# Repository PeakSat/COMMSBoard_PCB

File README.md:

# SatNOGS COMMS hardware

A CubeSat format ([LibreCube Board](https://wiki.librecube.org/index.php?title=LibreCube_Board_Specification)) COMMS board.
It supports UHF and S-Band concurrent half duplex (in each band) communication.
More details could be found [here](https://gitlab.com/librespacefoundation/satnogs-comms/satnogs-comms-design-doc).

Stable versions are tagging with TBD.

## Contribute
This is a KiCAD project thus merging can be tricky.
Coordinate with project engineers before starting any changes and take look at issues.

## EDA
KiCAD 6

Requires [lsf-kicad-lib](https://gitlab.com/librespacefoundation/lsf-kicad-lib) to be installed.
Set path LSF_KICAD_LIB to point to lsf-kicad-lib folder for 3D models to appear correctly

#### Schematic
Changes in manufacturer part numbers field, footprints and designators can be merged most of the times.
Any part change, change in placement, wire placement etc cannot be merged at this point.

One exception is Hierarchical sheets provided that:

* A single person is working on a Hierarchical sheet
* Annotation is using sheet number
* Global nets are respected
* Changes in Hierarchical labels are coordinated

#### PCB
At this point any merging on PCB files must be avoided.
Also for the PCB (*.kicad_pcb) is used [LFS](https://docs.gitlab.com/ee/topics/git/lfs/) to prevent
a large size repository and to use the feature of LFS lock. The LFS lock protects the developers
to have conflicts in PCB that aren't merged. For that reason use:

```
git lfs clone
```

to clone the repository.

## Simulation
[Qucs 0.0.20](https://github.com/Qucs/qucs).

## License
Licensed under the [CERN OHLv1.2](LICENSE)

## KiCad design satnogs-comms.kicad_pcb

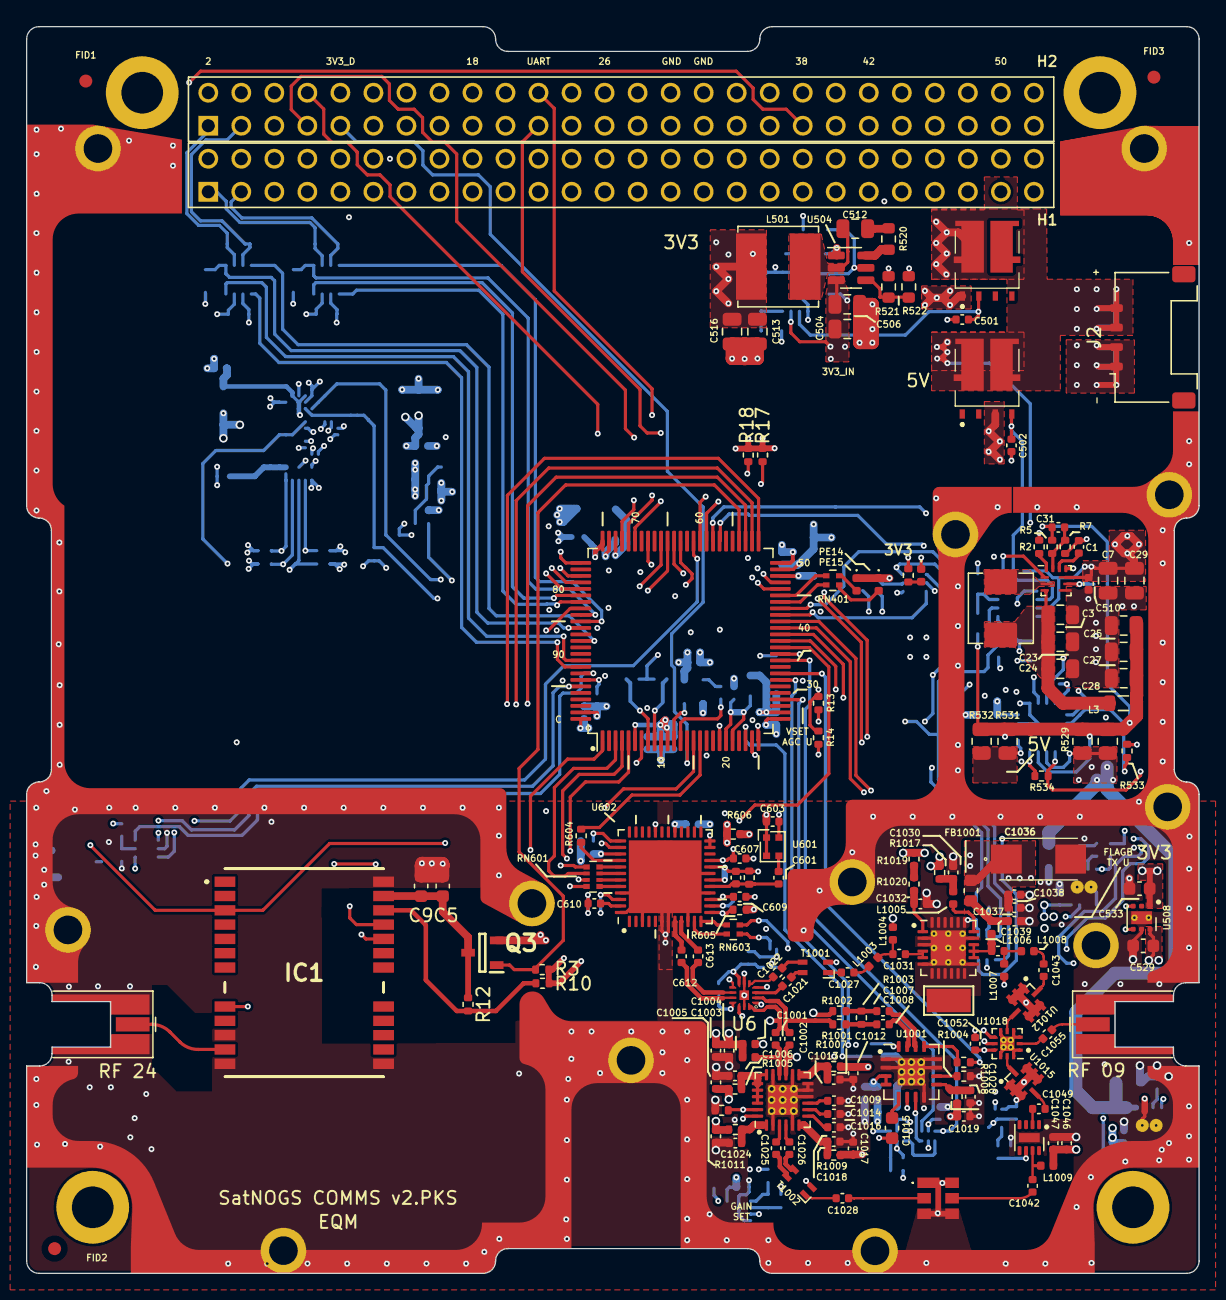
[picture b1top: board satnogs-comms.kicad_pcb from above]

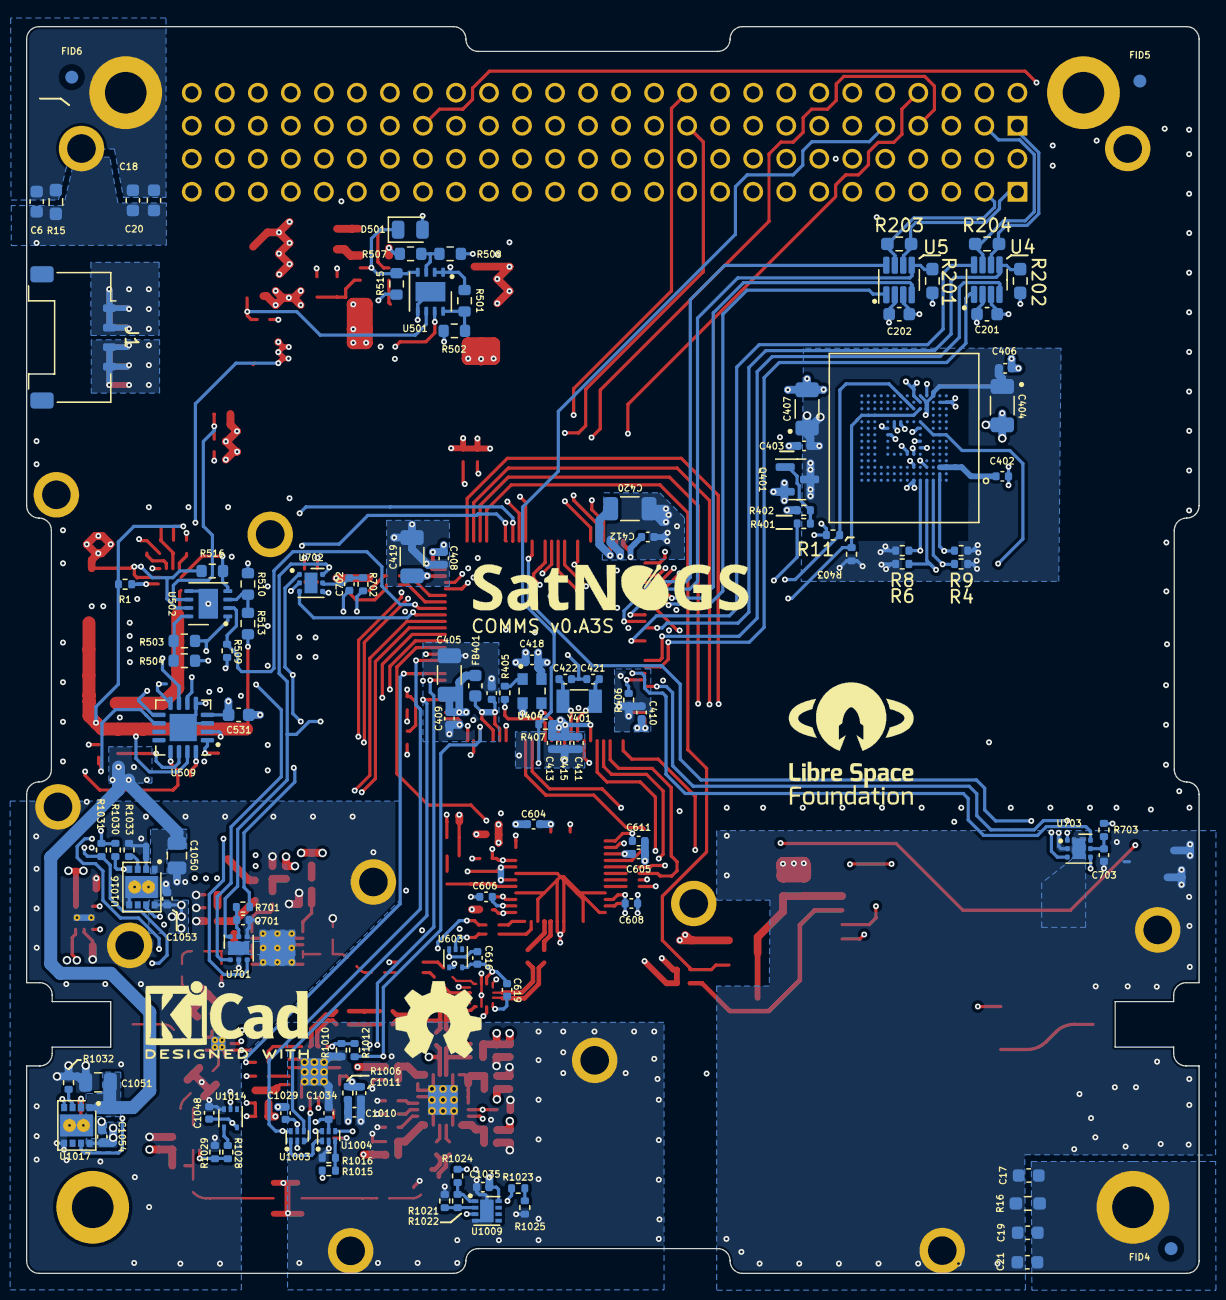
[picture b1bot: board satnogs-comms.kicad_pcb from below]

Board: 6 copper layers, 90.2 x 95.9 mm, 288 parts (124 on the bottom side), 202 nets.

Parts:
ANT-S901: RF 24; MMCX_Molex_73415-0961_Horizontal_1.6mm-PCB
ANT-U1001: RF 09; MMCX_Molex_73415-0961_Horizontal_1.6mm-PCB
C1: 470n; C_0402_1005Metric
C2, C31, C402, C403, C406, C408, C409, C410, C411, C412, C413, C415, C418, C501, C502, C603, C604, C605, C607, C608, C609, C701, C702, C703, C1003, C1005, C1010, C1012, C1017, C1019, C1023, C1030, C1048, C1053, C1054: 100n; C_0402_1005Metric
C3, C23, C24, C25, C27, C28: 22uF; C_0805_2012Metric
C5: 10u; C_0603_1608Metric
C6, C17, C18, C19, C20, C21: 1n; C_0603_1608Metric
C7, C29: 6.8u; C_0805_2012Metric
C9, C201, C202, C531: 100n; C_0603_1608Metric
C404, C405, C407: 4.7u; C_1206_3216Metric
C419, C420: 2.2u; C_1206_3216Metric
C421, C422: 12p; C_0402_1005Metric
C504, C1050, C1051: 10u; C_0805_2012Metric
C506, C512: 100n; C_0805_2012Metric
C510: 2.2n; C_0402_1005Metric
C513, C516: 22u; C_0805_2012Metric
C529, C533: 1u; C_0603_1608Metric
C601, C1007, C1008, C1009, C1014, C1016, C1037: 1n; C_0402_1005Metric
C602: 10p; C_0402_1005Metric
C606, C610, C611, C1046: 1u; C_0402_1005Metric
C612, C613, C616, C619, C1001, C1002, C1004, C1006, C1011, C1013, C1018, C1020, C1021, C1022, C1024, C1025, C1026, C1028, C1032, C1038, C1039, C1042, C1047, C1049, C1052, C1055: 100p; C_0402_1005Metric
C1015: 220pF; C_0603_1608Metric
C1027: 2p; C_0402_1005Metric
C1029, C1034, C1035: 10n; C_0402_1005Metric
C1031: 62p; C_0402_1005Metric
C1036: 10u; T495C
C1040: 24p; C_0402_1005Metric
C1043: 3.3p; C_0402_1005Metric
D401: PE14; LED_0402_1005Metric
D402: PE15; LED_0402_1005Metric
D501: 3.6V; D_0805_2012Metric
D502: 3V3; LED_0402_1005Metric
FB401, FB1001: Ferrite_Bead; L_0603_1608Metric
FID1, FID2, FID3, FID4, FID5, FID6: Fiducial; Fiducial_1mm_Mask2mm
FL2: SF2446E
H111, H112, H113, H114: MountingHole_Pad; MountingHole_3.2mm_M3_DIN965_Pad
IC1: B1601
J1, J2: Conn_01x04; Molex_Pico-Lock_504050-0491_1x04-1MP_P1.50mm_Horizontal
J102: Η1; ESQ-126-39-x-D
J103: Η2; ESQ-126-39-x-D
J104: RFShield_OnePiece; emi-shield-original
L2: 2.2u; L_Abracon_ASPI-0530HI
L3: 0u; L_0805_2012Metric
L501: 4.7u; L_Bourns_SRN6045TA
L1001, L1002: 120n; L_0402_1005Metric
L1003, L1005, L1009: 68n; L_0402_1005Metric
L1004: 3.2n; L_0402_1005Metric
L1006: 18n; L_0402_1005Metric
L1007: 8.2n; L_0402_1005Metric
L1008: 47n; L_0402_1005Metric
NT1, NT601, NT1001, NT1002: Net-Tie_2; NetTie-2_SMD_Pad0.5mm
Q1, Q2: SQJB90EP-T1_GE3; SQJ910AEPT1_GE3
Q3: PMV28XPEAR; SOT95P230X110-3N
Q401: FDN308P; SOT-23
R1, R402, R605, R1030, R1031: 100k; R_0402_1005Metric
R2: 18.2k; R_0402_1005Metric
R3, R4, R6, R8, R9, R11, R406, R509, R533, R534, R603, R1010, R1011, R1029: 10k; R_0402_1005Metric
R5: 25.5k; R_0402_1005Metric
R7: 4.87k; R_0402_1005Metric
R10, R405, R606, R1004, R1005, R1006, R1007, R1008, R1009, R1012, R1014, R1020, R1021, R1022, R1024: 0; R_0402_1005Metric
R12, R407: DNP; R_0402_1005Metric
R13, R14, R17, R18: 5k; R_0402_1005Metric
R15, R16: 100k; R_0603_1608Metric_Pad0.98x0.95mm_HandSolder
R201, R202: 10k; R_0603_1608Metric_Pad0.98x0.95mm_HandSolder
R203, R204: 120; R_0603_1608Metric_Pad0.98x0.95mm_HandSolder
R401, R1013, R1015, R1023: 1k; R_0402_1005Metric
R403: 4.7k; R_0402_1005Metric
R501: 200k; R_0603_1608Metric
R502, R504, R507: 100k; R_0603_1608Metric
R503: 345k; R_0603_1608Metric
R508: 620k; R_0603_1608Metric
R510: 73.2k; R_0603_1608Metric
R513: 706k; R_0603_1608Metric
R515, R516: 2.2k; R_0603_1608Metric
R520: 30; R_0603_1608Metric
R521: 30.9k; R_0603_1608Metric
R522: 10k; R_0603_1608Metric
R529, R530, R531, R532: 0.02; R_0805_2012Metric
R537: 330; R_0402_1005Metric
R604: 470; R_0402_1005Metric
R701, R702, R703: 500; R_0402_1005Metric
R1001, R1002: 82; R_0402_1005Metric
R1003: 52.3; R_0402_1005Metric
R1016: 412; R_0402_1005Metric
R1017: 240; R_0402_1005Metric
R1019: 280; R_0402_1005Metric
R1025: 2.2k; R_0402_1005Metric
R1028: 33k; R_0402_1005Metric
R1032: 374k; R_0402_1005Metric
R1033: 110k; R_0402_1005Metric
RN401: 330; R_Array_Convex_2x0402
RN601: 470; R_Array_Convex_4x0402
RN603: R_Pack02; R_Array_Convex_2x0402
T1001, T1002: Transformer_1P_1S; ATB2012
TP1011: TestPoint; TestPoint_Keystone_5015_Micro-Minature
U1: STM32H743VITx; LQFP-100_14x14mm_P0.5mm
U3: TPS62913; Texas_VQFN-10-HR_2x2_Pitch0.5mm
U4, U5: TCAN337G; SOT-23-8
U6: SKY13421-486LF; QFN-14-1EP_1.60x1.60mm_P0.40mm_EP0.74x0.74mm
U401: SDINBDG4-8G; BGA-153_13.0mmx11.5mm_P0.5mm
U404: ECS-TXO-2520-33-120-AN-TR; OSC_ECS-TXO-2520-33-120-AN-TR
U501, U502: MAX6497; Maxim_T833-2_TDFN-8-1EP_3x3mm_P0.65mm_EP1.5x2.3mm
U504: TPS56339; SOT-23-6
U508: LP5912-3.3DRV; WSON-6-1EP_2x2mm_P0.65mm_EP1x1.6mm_ThermalVias
U509: INA3221; Texas_RGV_S-PVQFN-N16_EP2.1x2.1mm
U601: KT1612A; KT1612
U602: AT86RF215; QFN-48-1EP_7x7mm_P0.5mm_EP5.6x5.6mm
U603, U1014: NL17SV04XV5T2G; SOT-553
U701, U702, U703: TMP117; WSON-6-1EP_2x2mm_P0.65mm_EP1x1.6mm
U1001: AD8318; QFN-16-1EP_4x4mm_P0.65mm_EP2.1x2.1mm_ThermalVias
U1002: ADL5330; LFCSP-24-1EP_4x4mm_P0.5mm_EP2.3x2.3mm_ThermalVias
U1003, U1004: NC7SB3157L6X; Fairchild_MicroPak-6_1.0x1.45mm_P0.5mm
U1006: TQP7M9106; QFN-24-1EP_4x4mm_P0.5mm_EP2.7x2.7mm_ThermalVias
U1009: TSV912IQ2T; DFN-8-1EP_2x2mm_P0.5mm_EP1.05x1.75mm
U1012: LFCG-490+; GE0805C-2
U1013: TQP3M9036; DFN-8-1EP_2x2mm_P0.5mm_EP0.7x1.6mm
U1015: LFCG-1400+; GE0805C-2
U1016, U1017: FPF2701; MLP-8
U1018: F2972; IDT_NEG-12-1EP_2x2mm_P0.5mm_EP1.1x1.1mm_ThermalVias
Y401: 32768Hz; Crystal_SMD_3215-2Pin_3.2x1.5mm

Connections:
3V3_D: C201.1, C202.1, C405.1, C408.1, C409.1, C410.1, C411.1, C412.1, C413.1, C415.1, C418.1, C513.2, C516.2, C531.2, FB401.1, J103.10, L501.2, Q401.2 (S), R13.1, R14.1, R17.1, R18.1, R201.1, R202.1, R402.1, R407.1, R508.1, R521.2, R533.2, R534.2, R537.1, R701.1, R702.1, R703.1, R1030.2, R1031.2, U1.6 (VBAT), U1.11 (VDD), U1.27 (VDD), U1.50 (VDD), U1.75 (VDD), U1.100 (VDD), U4.3 (VCC), U5.3 (VCC), U404.4 (VDD), U509.4 (VS), U509.16 (VPU)
3V3_RF: C533.1, C603.2, C616.2, C619.2, C1029.1, C1034.1, C1035.2, C1048.1, C1052.1, Q3.2 (S), R3.1, R10.2, R605.2, R606.1, U6.7 (VDD), U508.1 (OUT), U601.4 (Vcc), U603.5 (VCC), U1003.5 (V+), U1004.5 (V+), U1009.8 (V+), U1014.5 (VCC), U1018.9 (VCC)
5V_RF_S: R531.1, R532.1, U509.1 (IN-3)
5V_RF_U: C529.1, C1050.1, C1051.1, R529.1, R530.1, U508.6 (IN), U509.14 (IN-2), U1016.1 (VIN), U1017.1 (VIN)
/BUS_SCL: J102.43, U1.46 (PB10)
/BUS_SDA: J102.41, U1.47 (PB11)
/CAN/CAN1_FAULT: R201.2, U1.84 (PD3), U5.5 (FAULT)
/CAN/CAN1_RX: U1.81 (PD0), U5.4 (RXD)
/CAN/CAN1_S: U1.85 (PD4), U5.8 (S)
/CAN/CAN1_TX: U1.82 (PD1), U5.1 (TXD)
/CAN/CAN2_FAULT: R202.2, U1.86 (PD5), U4.5 (FAULT)
/CAN/CAN2_RX: U1.91 (PB5), U4.4 (RXD)
/CAN/CAN2_S: U1.88 (PD7), U4.8 (S)
/CAN/CAN2_TX: U1.92 (PB6), U4.1 (TXD)
/CAN_A+: J102.3, R203.1, U5.7 (CANH)
/CAN_A-: J102.1, R203.2, U5.6 (CANL)
/CAN_B+: J103.3, R204.1, U4.7 (CANH)
/CAN_B-: J103.1, R204.2, U4.6 (CANL)
/MCU/AGC_TEMP_UHF: R1013.1, U1.33 (PC5)
/MCU/ALERT_T_PA_S: U1.61 (PD14), U703.3 (ALERT)
/MCU/ALERT_T_PA_U: U1.38 (PE8), U701.3 (ALERT)
/MCU/ALERT_T_PCB: U1.42 (PE12), U702.3 (ALERT)
/MCU/AVDD: C2.1, NT1.1, U1.20 (VREF+)
/MCU/EN_AGC_UHF: U1.35 (PB1), U1003.6, U1004.6
/MCU/EN_AMP_RX_UHF: R1011.2, R1012.1, U1.23 (PA1), U1002.23 (ENBL), U1014.2
/MCU/EN_PA_UHF: R1030.1, U1.36 (PB2), U1016.4 (ON)
/MCU/EN_RX_UHF: R1031.1, U1.41 (PE11), U1017.4 (ON)
/MCU/FLAGB_RX_UHF: U1.40 (PE10), U1017.7 (FLAGB)
/MCU/FLAGB_TX_UHF: U1.39 (PE9), U1016.7 (FLAGB)
/MCU/GAIN_SET_UHF: R1024.1, U1.32 (PC4)
/MCU/GNSS_RSTN: IC1.8 (RSTN), U1.53 (PB14)
/MCU/GNSS_UART_RX: IC1.21 (RXD), U1.51 (PB12)
/MCU/GNSS_UART_TX: IC1.20 (TXD), U1.52 (PB13)
/MCU/I2C1_SCL: R14.2, U1.95 (PB8), U701.1 (SCL), U702.1 (SCL), U703.1 (SCL), U703.4 (ADD0)
/MCU/I2C1_SDA: R13.2, U1.93 (PB7), U701.6 (SDA), U702.4 (ADD0), U702.6 (SDA), U703.6 (SDA)
/MCU/I2C4_SCL: R17.2, U1.59 (PD12), U509.6 (SCL)
/MCU/I2C4_SDA: R18.2, U1.60 (PD13), U509.7 (SDA)
/MCU/LED_PE14: RN401.2 (R2.1), U1.44 (PE14)
/MCU/LED_PE15: RN401.1 (R1.1), U1.45 (PE15)
/MCU/MCU_MMC_CK: R11.1, U1.80 (PC12), U401.M6 (CLK), U401.N7, U401.P8
/MCU/MCU_MMC_CMD: R403.2, U1.83 (PD2), U401.L12, U401.L13, U401.L14, U401.M5 (CMD)
/MCU/MCU_MMC_D0: R4.2, U1.65 (PC8), U401.A3 (DAT0)
/MCU/MCU_MMC_D1: R6.2, U1.66 (PC9), U401.A4 (DAT1)
/MCU/MCU_MMC_D2: R8.2, U1.78 (PC10), U401.A5 (DAT2)
/MCU/MCU_MMC_D3: R9.2, U1.79 (PC11), U401.A2, U401.B2 (DAT3)
/MCU/MMC_EN: R401.2, U1.63 (PC6)
/MCU/MMC_RST: U1.7 (PC13), U401.H1, U401.H2, U401.H3, U401.K5 (RST_N)
/MCU/MONITOR_CRITICAL: U1.24 (PA2), U509.9 (CRITICAL)
/MCU/MONITOR_PG: R533.1, U1.57 (PD10), U509.10 (PV)
/MCU/MONITOR_TC: R534.1, U1.58 (PD11), U509.13 (TC)
/MCU/MONITOR_WARNING: U1.25 (PA3), U509.8 (WARNING)
/MCU/P3V3_RF_PG: U1.68 (PA9), U508.3 (PG)
/MCU/P5V_RF_EN: R509.1, U1.43 (PE13), U502.2 (~SHDN)
/MCU/P5V_RF_PG: R1.1, U1.64 (PC7), U3.5 (PG), U508.4 (EN)
/MCU/RCC_OSC32_IN: C421.2, U1.8 (PC14), Y401.1
/MCU/RCC_OSC32_OUT: C422.1, U1.9 (PC15), Y401.2
/MCU/RF_IRQ: R604.1, U1.16 (PC1)
/MCU/RF_RST: R605.1, U1.37 (PE7), U602.13 (RSTN)
/MCU/RF_SPI_MISO: RN601.4 (R4.1), U1.4 (PE5)
/MCU/RF_SPI_MOSI: RN601.3 (R3.1), U1.5 (PE6)
/MCU/RF_SPI_SCL: RN601.1 (R1.1), U1.1 (PE2)
/MCU/RF_SPI_SEL: RN601.2 (R2.1), U1.3 (PE4)
/MCU/TCXO_EN: R405.2, U1.13 (PH1)
/MCU/TCXO_OUT: U1.12 (PH0), U404.3 (OUTPUT)
/MCU/VDDI: C402.1, U401.C1, U401.C2 (VDDI)
/MCU/VSET_AGC_UHF: U1.29 (PA5), U1003.4
/Main PSU/G2mos: C502.1, Q1.4 (G2), U502.6 (GATT)
/Main PSU/GATE: C501.1, Q2.2 (G1), U501.6 (GATT)
/Main PSU/S2mos: C7.1, C29.1, C510.1, Q1.3 (S2), R516.1, U3.6 (VIN), U502.7 (OUTFB)
/RF/3.3V_AT: C604.2, C605.2, C607.2, C608.2, C609.2, R606.2, U602.15 (EVDD), U602.21 (DEVDD), U602.29 (DEVDD), U602.39 (DEVDD), U602.46 (EVDD)
/RF/RF09CAP_N: C613.2, U6.9 (RFCB)
/RF/RF09CAP_P: C612.2, U6.10 (RFCA)
/RF/RF09N: C613.1, U602.9 (RFN09)
/RF/RF09P: C612.1, U602.8 (RFP09)
/RF/SW_CTL_UHF: U6.12 (Vctl), U603.4, U1018.7 (Vctl)
/RF/SW_EN_UHF: RN603.2 (R2.1), U1018.8 (EN)
/RF/uhf-frontend/5V_RX_U: C1003.2, C1004.2, C1005.2, C1010.2, C1012.2, C1017.1, C1019.1, C1023.1, C1046.1, C1047.1, C1054.1, L1001.1, L1002.2, L1009.2, R1005.2, R1006.2, R1007.1, R1008.2, R1009.2, R1014.2, U1017.8 (VOUT)
/RF/uhf-frontend/5V_TX_U: C1036.1, C1037.1, C1038.1, C1053.1, FB1001.2, R1017.1, R1019.2, U1016.8 (VOUT)
/RF/uhf-frontend/GAIN_SET: R1023.2, U1002.24 (GAIN), U1004.4, U1009.3 (+)
/RF/uhf-frontend/RX09N: C1002.2, R1001.1, U6.2 (RF1B)
/RF/uhf-frontend/RX09P: C1001.1, R1002.2, U6.14 (RF1A)
/RF/uhf-frontend/RX09_DET_IPN: C1008.1, U1001.15 (INLO)
/RF/uhf-frontend/RX09_DET_IPP: C1007.2, U1001.14 (INHI)
/RF/uhf-frontend/RX09_VGA_IPN: C1026.1, T1002.3 (SA)
/RF/uhf-frontend/RX09_VGA_IPP: C1025.2, T1002.4 (SB)
/RF/uhf-frontend/RX09_VGA_OPN: C1002.1, L1001.2, U1002.15 (OPLO)
/RF/uhf-frontend/RX09_VGA_OPP: C1001.2, L1002.1, U1002.16 (OPHI)
/RF/uhf-frontend/TX09N: C1022.2, U6.5 (RF2B)
/RF/uhf-frontend/TX09P: C1021.2, U6.3 (RF2A)
AC_GND_1: C6.1, C18.1, C20.1, H112.1, R15.1
AC_GND_2: C17.1, C19.1, C21.1, H114.1, R16.1
GND: ANT-S901.2 (Ext), ANT-U1001.2 (Ext), C1.2, C2.2, C3.2, C5.2, C6.2, C7.2, C9.2, C17.2, C18.2, C19.2, C20.2, C21.2, C23.2, C24.2, C25.2, C27.2, C28.2, C29.2, C201.2, C202.2, C402.2, C403.2, C404.2, C405.2, C406.1, C407.1, C408.2, C409.2, C410.2, C411.2, C412.2, C413.2, C415.2, C418.2, C419.1, C420.1, C421.1, C422.2, C501.2, C502.2, C504.2, C506.2, C510.2, C513.1, C516.1, C529.2, C531.1, C533.2, C602.2, C603.1, C604.1, C605.1, C606.1, C607.1, C608.1, C609.1, C610.1, C611.1, C616.1, C619.1, C701.1, C702.1, C703.1, C1003.1, C1004.1, C1005.1, C1006.1, C1009.1, C1010.1, C1011.1, C1012.1, C1013.1, C1014.1, C1015.2, C1016.1, C1017.2, C1018.2, C1019.2, C1020.2, C1023.2, C1024.2, C1029.2, C1030.2, C1032.2, C1034.2, C1035.1, C1036.2, C1037.2, C1038.2, C1039.1, C1046.2, C1047.2, C1048.2, C1050.2, C1051.2, C1052.2, C1053.2, C1054.2, D401.1 (K), D402.1 (K), D501.2 (A), D502.1 (K), FL2.1 (GND_1), FL2.3 (GND_2), FL2.4 (GND_3), FL2.6 (GND_4), IC1.10 (GND_1), IC1.12 (GND_2), IC1.13 (GND_3), IC1.24 (GND_4), J1.3, J1.4, J2.1, J2.2, J103.29, J103.30, J103.32, J104.1 (Shield), L1004.2, L1007.2, NT601.2, NT1001.1, NT1002.1, R2.2, R7.2, R11.2, R15.2, R16.2, R406.1, R502.1, R504.1, R507.1, R509.2, R510.1, R522.1, R603.2, R1004.2, R1010.1, R1011.1, R1016.1, R1021.2, R1025.2, R1029.2, R1032.2, R1033.2, T1001.2 (AB), T1002.2 (AB), TP1011.1, U1.10 (VSS), U1.19 (VSSA), U1.26 (VSS), U1.49 (VSS), U1.74 (VSS), U1.99 (VSS), U3.4 (PGND), U3.7 (PSNS), U4.2 (GND), U5.2 (GND), U6.1 (GND), U6.4 (GND), U6.6 (GND), U6.8 (GND), U6.11 (GND), U6.13 (GND), U6.15 (EP), U401.A6 (VSS), U401.C4 (VSSQ), U401.E7 (VSS), U401.G5 (VSS), U401.H10 (VSS), U401.J5 (VSS), U401.K8 (VSS), U401.N1, U401.N2 (VSSQ), U401.N5 (VSSQ), U401.P4 (VSSQ), U401.P6 (VSSQ), U404.2 (GND), U501.5 (GND), U501.9 (EP), U502.5 (GND), U502.9 (EP), U504.1 (GND), U508.5 (GND), U508.7 (EP), U509.3 (GND), U509.5 (A0), U509.17 (EP), U601.1 (GND/Vcon), U601.2 (GND), U602.3 (AVSS), U602.6 (AVSS), U602.7 (AVSS), U602.10 (AVSS), U602.16 (AVSS), U602.19 (AVSS), U602.20 (DVSS), U602.23 (DVSS), U602.24 (DVSS), U602.32 (DVSS), U602.38 (DVSS), U602.45 (AVSS), U602.48 (AVSS), U602.49 (EP), U603.3 (GND), U701.2 (GND), U701.4 (ADD0), U701.7 (EP), U702.2 (GND), U703.2 (GND), U703.7 (EP), U1001.1 (CMIP), U1001.2 (CMIP), U1001.8 (CMOP), U1001.11 (CMIP), U1001.12 (CMIP), U1001.17 (EPAD), U1002.2 (COM1), U1002.5 (COM1), U1002.10 (COM1), U1002.11 (GNLO), U1002.12 (COM2), U1002.14 (COM2), U1002.17 (COM2), U1002.25 (EP), U1003.2 (GND), U1004.2 (GND), U1006.2 (GND), U1006.3 (GND), U1006.6 (GND), U1006.7 (GND), U1006.8 (GND), U1006.9 (GND), U1006.10 (GND), U1006.11 (GND), U1006.12 (GND), U1006.13 (GND), U1006.17 (GND), U1006.19 (GND), U1006.20 (GND), U1006.21 (GND), U1006.22 (GND), U1006.23 (GND), U1006.24 (GND), U1006.25 (EP), U1009.4 (V-), U1009.9 (PAD), U1012.1 (GND), U1012.2 (GND), U1012.3 (GND), U1012.5 (GND), U1012.6 (GND), U1012.7 (GND), U1013.9 (GND), U1014.3 (GND), U1015.1 (GND), U1015.2 (GND), U1015.3 (GND), U1015.5 (GND), U1015.6 (GND), U1015.7 (GND), U1016.5 (GND), U1016.9 (GND), U1017.5 (GND), U1017.9 (GND), U1018.1 (GND), U1018.3 (GND), U1018.4 (GND), U1018.6 (GND), U1018.10 (GND), U1018.12 (GND), U1018.13 (GND)
GNSS_ENABLE: Q3.1 (G), R3.2, U1.54 (PB15)
GNSS_PPS: IC1.3 (1PPS_), J103.37, U1.15 (PC0)
JTCK-SWCLK: J103.8, U1.76 (PA14)
JTMS-SWDIO: J103.7, U1.72 (PA13)
MCU_NRSTD: J103.9, R407.2, U1.14 (NRST)
unnamed: ANT-S901.1 (In), IC1.11 (RF_IN)
unnamed: ANT-U1001.1 (In), C1055.1
unnamed: C419.2, U1.48 (VCAP)
unnamed: C420.2, U1.73 (VCAP)
unnamed: C512.2, R520.1
unnamed: C1006.2, R1005.1, U1002.18 (VPS2), U1002.19 (VPS2), U1002.20 (VPS2), U1002.21 (VPS2), U1002.22 (VPS2)
unnamed: C1007.1, R1002.1, R1003.2
unnamed: C1008.2, R1001.2, R1003.1
unnamed: C1011.2, R1006.1, U1001.3 (VPSI), U1001.4 (VPSI)
unnamed: C1013.2, R1007.2, U1002.13 (VPS2)
unnamed: C1018.1, R1009.1, U1002.6 (VPS1)
unnamed: C1024.1, R1014.1, U1002.1 (VPS1)
unnamed: C1027.2, L1003.1
unnamed: C1030.1, L1005.2, R1017.2
unnamed: C1031.1, L1003.2, L1004.1
unnamed: C1031.2, U1006.4 (RFIN), U1006.5 (RFIN)
unnamed: C1039.2, FB1001.1, L1006.1
unnamed: C1040.1, L1006.2, U1006.14 (RFOUT/VCC), U1006.15 (RFOUT/VCC), U1006.16 (RFOUT/VCC)
unnamed: C1040.2, L1007.1, L1008.1
unnamed: C1043.1, L1008.2
unnamed: D401.2 (A), RN401.3 (R2.2)
unnamed: D402.2 (A), RN401.4 (R1.2)
unnamed: D501.1 (K), R515.2, U501.4 (POK), U504.5 (EN)
unnamed: D502.2 (A), R537.2
unnamed: C1028.2, FL2.2 (INPUT)
unnamed: C1042.1, FL2.5 (OUTPUT)
unnamed: C5.1, C9.1, IC1.23 (VCC), Q3.3 (D), R12.1
unnamed: IC1.22 (V_BCKP), R10.1, R12.2
unnamed: C504.1, C506.1, Q2.1 (S1), R515.1, U501.7 (OUTFB), U504.3 (VIN)
unnamed: C403.1, C404.1, C406.2, C407.2, Q401.3 (D), R4.1, R6.1, R8.1, R9.1, R403.1, U401.C6 (VCCQ), U401.E6 (VCC), U401.F5 (VCC), U401.J10 (VCC), U401.K9 (VCC), U401.M4 (VCCQ), U401.N4 (VCCQ), U401.P3 (VCCQ), U401.P5 (VCCQ)
unnamed: Q401.1 (G), R401.1, R402.2
unnamed: R1015.1, R1016.2, U1004.3
unnamed: R1019.1, R1020.2
unnamed: R1022.1, R1024.2, U1009.1
unnamed: R1023.1, R1025.1
unnamed: R1028.2, U1014.4
unnamed: RN601.8 (R1.2), U602.41 (SCLK)
unnamed: RN601.7 (R2.2), U602.42 (SELN)
unnamed: RN601.6 (R3.2), U602.43 (MOSI)
unnamed: RN601.5 (R4.2), U602.44 (MISO)
unnamed: RN603.1 (R1.1), U603.2
unnamed: RN603.4 (R1.2), U602.11 (FEA09)
unnamed: RN603.3 (R2.2), U602.12 (FEB09)
unnamed: C1027.1, T1001.1 (AA)
unnamed: C1022.1, T1001.3 (SA)
unnamed: C1021.1, T1001.4 (SB)
unnamed: C1028.1, T1002.1 (AA)
unnamed: R406.2, U1.94 (BOOT0)
unnamed: FB401.2, NT1.2, U1.21 (VDDA)
unnamed: R516.2, U3.1 (EN/SYNC), U502.4 (POK)
unnamed: C31.2, R5.2, R7.1, U3.9 (FB)
unnamed: C1.1, U3.8 (NR/SS)
unnamed: R2.1, U3.10 (S-CONF)
unnamed: L2.1, U3.2 (SW)
unnamed: C3.1, C23.1, C24.1, L2.2, L3.1, U3.3 (VO)
unnamed: R405.1, U404.1 (TRI-STATE)
unnamed: R507.2, R508.2, U501.3 (OVSET)
unnamed: R501.1, R502.2, U501.8 (POKSET)
unnamed: R510.2, R513.2, U502.3 (OVSET)
unnamed: R503.1, R504.2, U502.8 (POKSET)
unnamed: R520.2, U504.6 (BOOT)
unnamed: R521.1, R522.2, U504.4 (FB)
unnamed: C512.1, L501.1, U504.2 (SW)
unnamed: C25.1, C27.1, C28.1, C31.1, L3.2, R1.2, R5.1, R513.1, R529.2, R530.2, R531.2, R532.2, U509.2 (IN+3), U509.15 (IN+2)
unnamed: C601.2, U601.3 (OUT)
unnamed: C606.2, U602.14 (AVDD0)
unnamed: C610.2, U602.47 (AVDD1)
unnamed: C611.2, U602.37 (DVDD)
unnamed: R604.2, U602.40 (IRQ)
unnamed: C601.1, C602.1, R603.1, U602.17 (TCXO)
unnamed: NT601.1, U602.18 (XTAL2)
unnamed: C701.2, R701.2, U701.5 (V+)
unnamed: C702.2, R702.2, U702.5 (V+)
unnamed: C703.2, R703.2, U703.5 (V+)
unnamed: C1015.1, U1001.5 (CLPF)
unnamed: R1010.2, R1012.2, U1001.16 (ENBL)
unnamed: R1004.1, U1001.10 (TADJ)
unnamed: R1013.2, U1001.13 (TEMP)
unnamed: R1015.2, U1001.6 (VOUT)
unnamed: C1020.1, R1008.1, U1001.9 (VPSO)
unnamed: U1001.7 (VSET), U1003.3
unnamed: C1025.1, U1002.3 (INHI)
unnamed: C1026.2, U1002.4 (INLO)
unnamed: C1014.2, U1002.8 (IPBS)
unnamed: C1009.2, U1002.9 (OPBS)
unnamed: C1016.2, U1002.7 (VREF)
unnamed: U1003.1, U1004.1
unnamed: L1005.1, U1006.18 (IREF)
unnamed: C1032.1, R1020.1, U1006.1 (VBIAS)
unnamed: R1021.1, R1022.2, U1009.2 (-)
unnamed: U1012.4 (IN), U1018.5 (RF1)
unnamed: C1043.2, U1012.8 (OUT)
unnamed: C1049.2, U1013.2 (RFIN)
unnamed: C1042.2, L1009.1, U1013.7 (RFOUT)
unnamed: R1028.1, R1029.1, U1013.6 (Shut_Down)
unnamed: C1049.1, U1015.4 (IN)
unnamed: U1015.8 (OUT), U1018.11 (RF2)
unnamed: R1033.1, U1016.3 (ISET)
unnamed: NT1001.2, U1016.2 (PGOOD)
unnamed: R1032.1, U1017.3 (ISET)
unnamed: NT1002.2, U1017.2 (PGOOD)
unnamed: C1055.2, U1018.2 (RFC)
UART_RX: J103.21, U1.70 (PA11)
UART_TX: J103.22, U1.71 (PA12)
VIN: J1.1, J1.2, J2.3, J2.4, Q1.5 (D1), Q1.6 (D2), Q1.7, Q1.8, Q1.9, Q1.10, Q2.5 (D1), Q2.8, Q2.9, R501.2, R503.2, U501.1 (IN), U501.2 (~SHDN), U502.1 (IN)

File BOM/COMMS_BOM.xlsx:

Designator | Footprint | Quantity | Value
ANT-S901 | MMCX_Molex_73415-0961_Horizontal_1.6mm-PCB | 1.0 | RF 24 | 73415-0961
ANT-U1001 | MMCX_Molex_73415-0961_Horizontal_1.6mm-PCB | 1.0 | RF 09 | 73415-0961
C1 | 0402 | 1.0 | 470n | C1005X5R1V474KBC
C1001, C1002, C1004, C1006, C1011, C1013, C1018, C1020, C1021, C1022, C1024, C1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 | 0402 | 26.0 | 100p | CBR04C101J3GAC
C1003, C1005, C1010, C1012, C1017, C1019, C1023, C1030, C1048, C1053, C1054, C2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 | 0402 | 35.0 | 100n | C0402C104K4RACTU
C1007, C1008, C1009, C1014, C1016, C1037, C601 | 0402 | 7.0 | 1n | C0402C102K8RACAUTO
C1015 | 0603 | 1.0 | 220pF | CL10C221JB8NNNC
C1027 | 0402 | 1.0 | 2p | GJM1555C1H2R0WB01D
C1029, C1034, C1035 | 0402 | 3.0 | 10n | C0402C103K9RACTU
C1031 | 0402 | 1.0 | 62p | 04025A620FAT2A
C1036 | T495C | 1.0 | 10u | T495C106K035ATE400
C1040 | 0402 | 1.0 | 24p | 04025U240FAT2A
C1043 | 0402 | 1.0 | 3.3p | GJM1555C1H3R3WB01D
C1046, C606, C610, C611 | 0402 | 4.0 | 1u | C0402C105K8PAC7411
C1050, C1051, C504 | 0805 | 3.0 | 10u | EMK212BB7106KG-T
C17, C18, C19, C20, C21, C6 | 0603 | 6.0 | 1n | C0603X102K5GACAUTO
C201, C202, C531, C9 | 0603 | 4.0 | 100n | C0603C104K9RACTU
C23, C24, C25, C27, C28, C3 | 0805 | 6.0 | 22uF | GRM21BR61A226ME44L
C29, C7 | 0805 | 2.0 | 6.8u | C2012X5R1E685K125AC
C404, C405, C407 | 1206.0 | 3.0 | 4.7u | TAJA475K016R
C419, C420 | 1206.0 | 2.0 | 2.2u | AC1206KKX7R7BB225
C421, C422 | 0402 | 2.0 | 12p | CBR04C120F3GAC
C5 | 0603 | 1.0 | 10u | EMK107BC6106MA-T
C506, C512 | 0805 | 2.0 | 100n | C0805C104M5RACTU
C510 | 0402 | 1.0 | 2.2n | CGA2B2X7R1H222K050BA
C513, C516 | 0805 | 2.0 | 22u | GRM21BR61A226ME44L
C529, C533 | 0603 | 2.0 | 1u | EMK107B7105KA-T
C602 | 0402 | 1.0 | 10p | C0402C100C8GACTU
D401 | 0402 | 1.0 | PE14 | FHA1105P-TR
D402 | 0402 | 1.0 | PE15 | FHA1105P-TR
D501 | 0805 | 1.0 | 3.6V | BZY55B3V6 RBG
D502 | 0402 | 1.0 | 3V3 | APHHS1005LQBC/D-V
FB1001, FB401 | 0603 | 2.0 | Ferrite_Bead | BLM18KG331SN1D
FL2 | SF2446E | 1.0 | SF2446E | RF1419D
IC1 | B1601 | 1.0 | Orion B16 | GNSS module
J1, J2 | Molex_Pico-Lock_504050-0491_1x04-1MP_P1.50mm_Horizontal | 2.0 | Conn_01x04 | 504050-0491
J102 | ESQ-126-39-x-D | 1.0 | Η1 | SSQ-126-03-G-D
J103 | ESQ-126-39-x-D | 1.0 | Η2 | SSQ-126-03-G-D
L1001, L1002 | 0402 | 2.0 | 120n | LQG15WHR12G02D
L1003, L1005, L1009 | 0402 | 3.0 | 68n | MHQ1005P68NGTD25
L1004 | 0402 | 1.0 | 3.2n | LQG15WZ3N2B02D
L1006 | 0402 | 1.0 | 18n | LQW15AN18NJ80D
L1007 | 0402 | 1.0 | 8.2n | MHQ1005P8N2GT000
L1008 | 0402 | 1.0 | 47n | AISC-0402-47NG-T
L2 | L_Abracon_ASPI-0530HI | 1.0 | 2.2u | ASPI-0520LR-2R2M-T2
L3 | 0805 | 1.0 | 0u | 7.828532E8
L501 | L_Bourns_SRN6045TA | 1.0 | 4.7u | SRN6045-4R7Y
Q1, Q2 | SQJ910AEPT1_GE3 | 2.0 | SQJB90EP-T1_GE3 | SQJB90EP-T1_GE3
Q3 | SOT95P230X110-3N | 1.0 | PMV28XPEAR | PMV28XPEAR
Q401 | SOT-23 | 1.0 | FDN308P | FDN308P
R1, R1030, R1031, R402, R605 | 0402 | 5.0 | 100k | CR0402-FX-1003GLF
R10, R1004, R1005, R1006, R1007, R1008, R1009, R1012, R1014, R1020, R1021, R102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 | 0402 | 15.0 | 0.0 | RC0402JR-070R
R1001, R1002 | 0402 | 2.0 | 82.0 | ERA-2AEB820X
R1003 | 0402 | 1.0 | 52.3 | RG1005P-52R3-B-T5
R1010, R1011, R1029, R11, R3, R4, R406, R509, R533, R534, R6, R603, R8, R9 | 0402 | 14.0 | 10k | CRCW040210K0FKEDC
R1013, R1015, R1023, R401 | 0402 | 4.0 | 1k | CRCW04021K00FKEDC
R1016 | 0402 | 1.0 | 412.0 | CRCW0402412RFKED
R1017 | 0402 | 1.0 | 240.0 | CRCW0402240RFKEDC
R1019 | 0402 | 1.0 | 280.0 | RC0402FR-07280RL
R1025 | 0402 | 1.0 | 2.2k | CRCW04022K20JNEDC
R1028 | 0402 | 1.0 | 33k | CR0402-FX-3302GLF
R1032 | 0402 | 1.0 | 374k | CRCW0402374KFKED
R1033 | 0402 | 1.0 | 110k | CRCW0402110KFKED
R12, R407 | 0402 | 2.0 | DNP
R13, R14, R17, R18 | 0402 | 4.0 | 5k | RC0402FR-075KL
R15, R16, R502, R504, R507 | 0603 | 5.0 | 100k | ERJ-3EKF1003V
R2 | 0402 | 1.0 | 18.2k | CRCW040218K2FKED
R201, R202, R522 | 0603 | 3.0 | 10k | CRCW060310K0FKECC
R203, R204 | 0603 | 2.0 | 120.0 | ERJ-3EKF1200V
R403 | 0402 | 1.0 | 4.7k | CRCW04024K70FKEDC
R5 | 0402 | 1.0 | 25.5k | CRCW040225K5FKED
R501 | 0603 | 1.0 | 200k | ERJ-H3ED2003V
R503 | 0603 | 1.0 | 345k | RN731JTTD3443F100
R508 | 0603 | 1.0 | 620k | CPF0603B620KE
R510 | 0603 | 1.0 | 73.2k | RT0603FRE0773K2L
R513 | 0603 | 1.0 | 706k | RN73H1JTTD7063D100
R515, R516 | 0603 | 2.0 | 2.2k | CR0603-JW-222ELF
R520 | 0603 | 1.0 | 30.0 | RC0603FR-0730RL
R521 | 0603 | 1.0 | 30.9k | ERJ-U03F3092V
R529, R530, R531, R532 | 0805 | 4.0 | 0.02 | RCWH080520L0FMEA
R537 | 0402 | 1.0 | 330.0 | ERA-2AED331X
R604 | 0402 | 1.0 | 470.0 | CRCW0402470RFKEDC
R7 | 0402 | 1.0 | 4.87k | CRCW04024K87FKEDC
R701, R702, R703 | 0402 | 3.0 | 500.0 | RR0510P-511-D
RN401 | R_Array_Convex_2x0402 | 1.0 | 330.0 | EXB-24V331JX
RN601 | R_Array_Convex_4x0402 | 1.0 | 470.0 | EXB-28V471JX
RN603 | R_Array_Convex_2x0402 | 1.0 | R_Pack02 | EXB-24VR000X
T1001, T1002 | ATB2012 | 2.0 | Transformer_1P_1S | ATB2012-50011-T000
U1 | LQFP-100_14x14mm_P0.5mm | 1.0 | STM32H743VITx
U1001 | QFN-16-1EP_4x4mm_P0.65mm_EP2.1x2.1mm_ThermalVias | 1.0 | AD8318 | AD8318ACPZ-REEL7
U1002 | LFCSP-24-1EP_4x4mm_P0.5mm_EP2.3x2.3mm_ThermalVias | 1.0 | ADL5330 | ADL5330ACPZ-REEL7
U1003, U1004 | Fairchild_MicroPak-6_1.0x1.45mm_P0.5mm | 2.0 | NC7SB3157L6X | NC7SB3157L6X
U1006 | QFN-24-1EP_4x4mm_P0.5mm_EP2.7x2.7mm_ThermalVias | 1.0 | TQP7M9106 | TQP7M9106
U1009 | DFN-8-1EP_2x2mm_P0.5mm_EP1.05x1.75mm | 1.0 | TSV912IQ2T | TSV912IQ2T
U1012 | GE0805C-2 | 1.0 | LFCG-490+ | LFCG-490+
U1013 | DFN-8-1EP_2x2mm_P0.5mm_EP0.7x1.6mm | 1.0 | TQP3M9036 | TQP3M9036
U1014, U603 | SOT-553 | 2.0 | NL17SV04XV5T2G | NL17SV04XV5T2G
U1015 | GE0805C-2 | 1.0 | LFCG-1400+ | LFCG-1400+
U1016, U1017 | MLP-8 | 2.0 | FPF2701MPX | FPF2701MPX
U1018 | IDT_NEG-12-1EP_2x2mm_P0.5mm_EP1.1x1.1mm_ThermalVias | 1.0 | F2972 | F2972
U3 | Texas_VQFN-10-HR_2x2_Pitch0.5mm | 1.0 | TPS62913 | TPS62913
U4, U5 | SOT-23-8 | 2.0 | TCAN337G | TCAN337GDCNT
U401 | BGA-153_13.0mmx11.5mm_P0.5mm | 1.0 | SDINBDG4-8G | SDINBDG4-8G
U404 | OSC_ECS-TXO-2520-33-120-AN-TR | 1.0 | ECS-TXO-2520-33-120-AN-TR | ECS-TXO-2520-33-120-AN-TR
U501, U502 | Maxim_T833-2_TDFN-8-1EP_3x3mm_P0.65mm_EP1.5x2.3mm | 2.0 | MAX6497 | MAX6497ATA+T
U504 | SOT-23-6 | 1.0 | TPS56339 | TPS56339DDCR
U508 | WSON-6-1EP_2x2mm_P0.65mm_EP1x1.6mm_ThermalVias | 1.0 | LP5912-3.3DRV | LP5912-3.3DRV
U509 | Texas_RGV_S-PVQFN-N16_EP2.1x2.1mm | 1.0 | INA3221 | INA3221
U6 | QFN-14-1EP_1.60x1.60mm_P0.40mm_EP0.74x0.74mm | 1.0 | SKY13421-486LF | SKY13421-486LF
U601 | KT1612 | 1.0 | KT1612A | KT1612A26000AAW18TBL
U602 | QFN-48-1EP_7x7mm_P0.5mm_EP5.6x5.6mm | 1.0 | AT86RF215 | AT86RF215-ZUR
U701, U702, U703 | WSON-6-1EP_2x2mm_P0.65mm_EP1x1.6mm | 3.0 | TMP117 | TMP117NAIDRVR
Y401 | Crystal_SMD_3215-2Pin_3.2x1.5mm | 1.0 | 32768Hz | ABS07-32.768KHZ-7-T

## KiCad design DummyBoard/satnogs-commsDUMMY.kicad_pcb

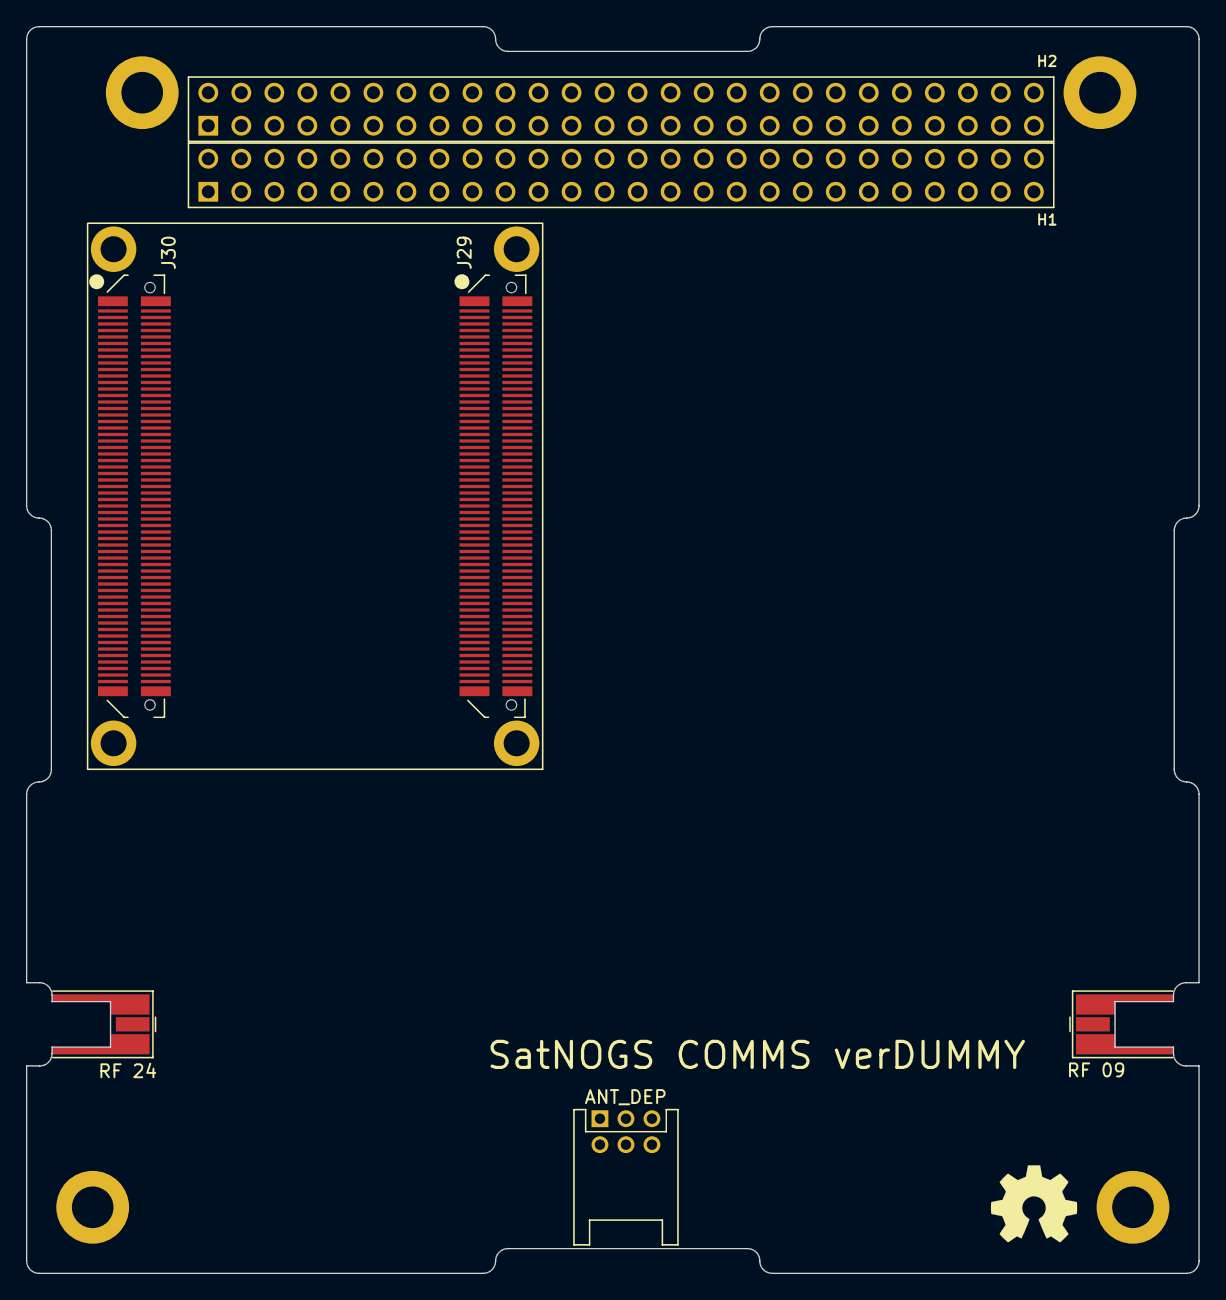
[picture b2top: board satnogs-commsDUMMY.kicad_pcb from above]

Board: 2 copper layers, 90.2 x 95.9 mm, 10 parts (0 on the bottom side), 4 nets, no tracks yet.

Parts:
ANT-S901: RF 24; MMCX_Molex_73415-0961_Horizontal_1.6mm-PCB
ANT-U1001: RF 09; MMCX_Molex_73415-0961_Horizontal_1.6mm-PCB
H111, H112, H113, H114: MountingHole_Pad; MountingHole_3.2mm_M3_DIN965_Pad
J101: ANT_DEP; hrs-df11-6dp-2ds
J102: Η1; ESQ-126-39-x-D
J103: Η2; ESQ-126-39-x-D
U301: Alinx_ZYNQ-7000_SOM_XC7Z020

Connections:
2V5_FPGA: U301.12 (VCCIO_35), U301.14 (VCCIO_35), U301.16 (VCCIO_35), U301.18 (VCCIO_35)
3V3_FPGA: U301.11 (VCCIO_34), U301.13 (VCCIO_34), U301.15 (VCCIO_34), U301.17 (VCCIO_34)
5V_FPGA: U301.1 (VCC5V), U301.2 (VCC5V), U301.3 (VCC5V), U301.4 (VCC5V), U301.5 (VCC5V), U301.6 (VCC5V), U301.7 (VCC5V), U301.8 (VCC5V)
GND: ANT-S901.2 (Ext), ANT-U1001.2 (Ext), J101.5, J101.6, J102.33, J102.34, J103.29, J103.30, J103.31, J103.32, U301.9 (GND), U301.10 (GND), U301.19 (GND), U301.20 (GND), U301.29 (GND), U301.30 (GND), U301.39 (GND), U301.40 (GND), U301.49 (GND), U301.50 (GND), U301.59 (GND), U301.60 (GND), U301.69 (GND), U301.70 (GND), U301.79 (GND), U301.80 (GND), U301.89 (GND), U301.90 (GND), U301.99 (GND), U301.100 (GND), U301.109 (GND), U301.110 (GND), U301.129 (GND-T13), U301.130 (GND-T13), U301.139 (GND-T13), U301.140 (GND-T13), U301.149 (GND-T13), U301.150 (GND-T13), U301.159 (GND-T13), U301.160 (GND-T13), U301.169 (GND-T13), U301.170 (GND-T13), U301.179 (GND-T13), U301.180 (GND-T13), U301.189 (GND-T13), U301.190 (GND-T13), U301.199 (GND-T13), U301.200 (GND-T13), U301.209 (GND-T13), U301.210 (GND-T13), U301.219 (GND-T13), U301.220 (GND-T13), U301.229 (GND-T13), U301.230 (GND-T13)

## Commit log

2024-04-11 Finalised Schematic
2024-04-15 Resolved issues
2024-04-16 Updated PC104 connector
2024-04-17 Fixed all ERC Errors & Warnings
2024-04-17 Updated all footprints
2024-04-18 Added Molex footprints
2024-04-19 Finished layout
2024-04-19 Resolved errors
2024-04-22 changed vias to burried in BGA region
2024-04-22 Added missing shield
2024-04-22 Resolve issues #6-#8
2024-04-22 Silkscreen update
2024-04-22 Gerbers updated
2024-04-22 Minor Update
2024-04-22 Remove Test points
2024-04-25 Silkscreen updates
2024-04-25 Minor updates
2024-04-29 Generated BOM
2024-06-04 Add POS files
2024-10-11 PCB: PC104 Update
2024-10-21 PSU: Add 2.2u soft-start capacitor on RF DCDC converter
2024-10-21 Add SWOTRACE pin to PC104
2024-10-21 PCB: Expose BOOT selection pin
2024-10-22 Add FM Gerbers
2024-10-29 Update FM BOM
2024-11-27 Update BOM
